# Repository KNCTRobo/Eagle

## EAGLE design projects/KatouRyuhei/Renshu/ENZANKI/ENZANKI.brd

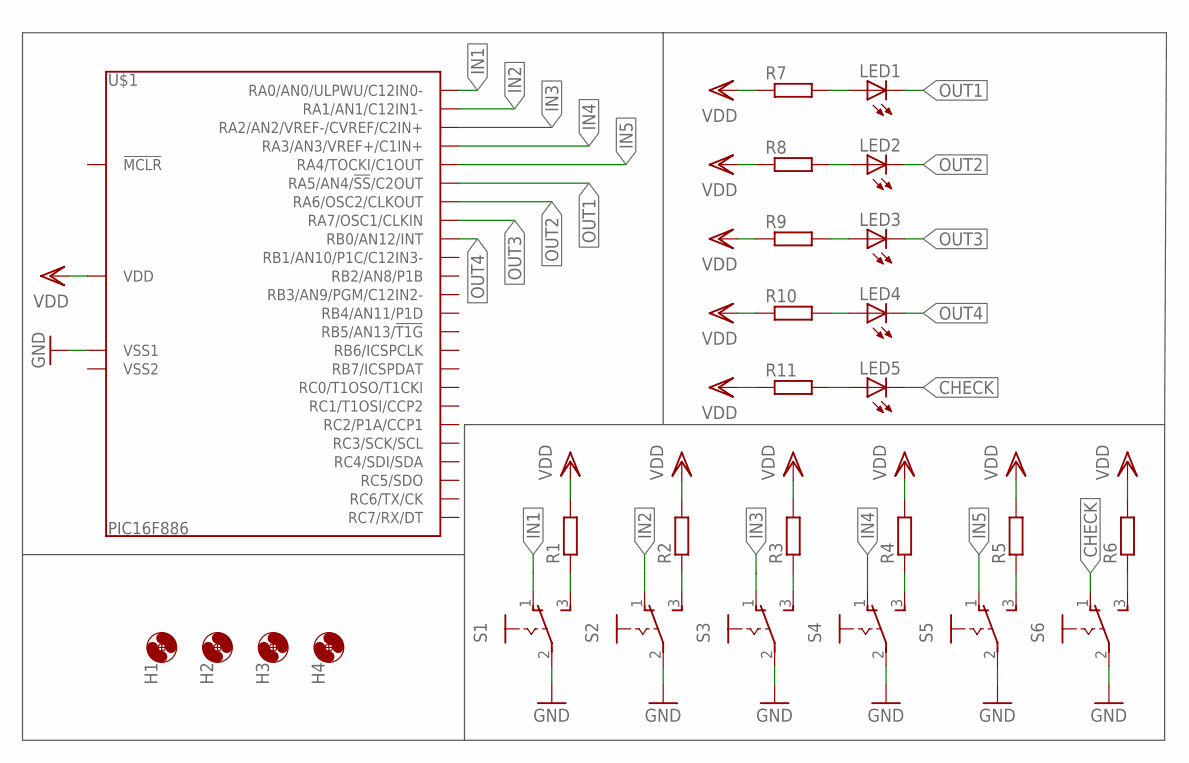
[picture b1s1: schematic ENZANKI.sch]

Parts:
H1, H2, H3, H4: HOLE3.3M3BOLT; HOLE3.3
LED1, LED2, LED3, LED4, LED5: LED5MM
R1, R2, R3, R4, R5, R6, R7, R8, R9, R10, R11: R-EU_R3216W; R3216W
S1, S2, S3, S4, S5, S6: SLIDESW
U$1: PIC16F886; DIL28

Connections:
CHECK: LED5.K (C), S6.1
GND: S1.2, S2.2, S3.2, S4.2, S5.2, S6.2, U$1.8 (VSS1)
IN1: S1.1, U$1.2 (RA0/AN0/ULPWU/C12IN0-)
IN2: S2.1, U$1.3 (RA1/AN1/C12IN1-)
IN3: S3.1, U$1.4 (RA2/AN2/VREF-/CVREF/C2IN+)
IN4: S4.1, U$1.5 (RA3/AN3/VREF+/C1IN+)
IN5: S5.1, U$1.6 (RA4/TOCKI/C1OUT)
unnamed: LED1.A, R7.2
unnamed: LED2.A, R8.2
unnamed: LED3.A, R9.2
unnamed: LED4.A, R10.2
unnamed: R6.1, S6.3
unnamed: R2.1, S2.3
unnamed: R3.1, S3.3
unnamed: R4.1, S4.3
unnamed: LED5.A, R11.2
unnamed: R5.1, S5.3
OUT1: LED1.K (C), U$1.7 (RA5/AN4/!SS!/C2OUT)
OUT2: LED2.K (C), U$1.10 (RA6/OSC2/CLKOUT)
OUT3: LED3.K (C), U$1.9 (RA7/OSC1/CLKIN)
OUT4: LED4.K (C), U$1.21 (RB0/AN12/INT)
R1: R1.1, S1.3
VDD: R1.2, R2.2, R3.2, R4.2, R5.2, R6.2, R7.1, R8.1, R9.1, R10.1, R11.1, U$1.20 (VDD)

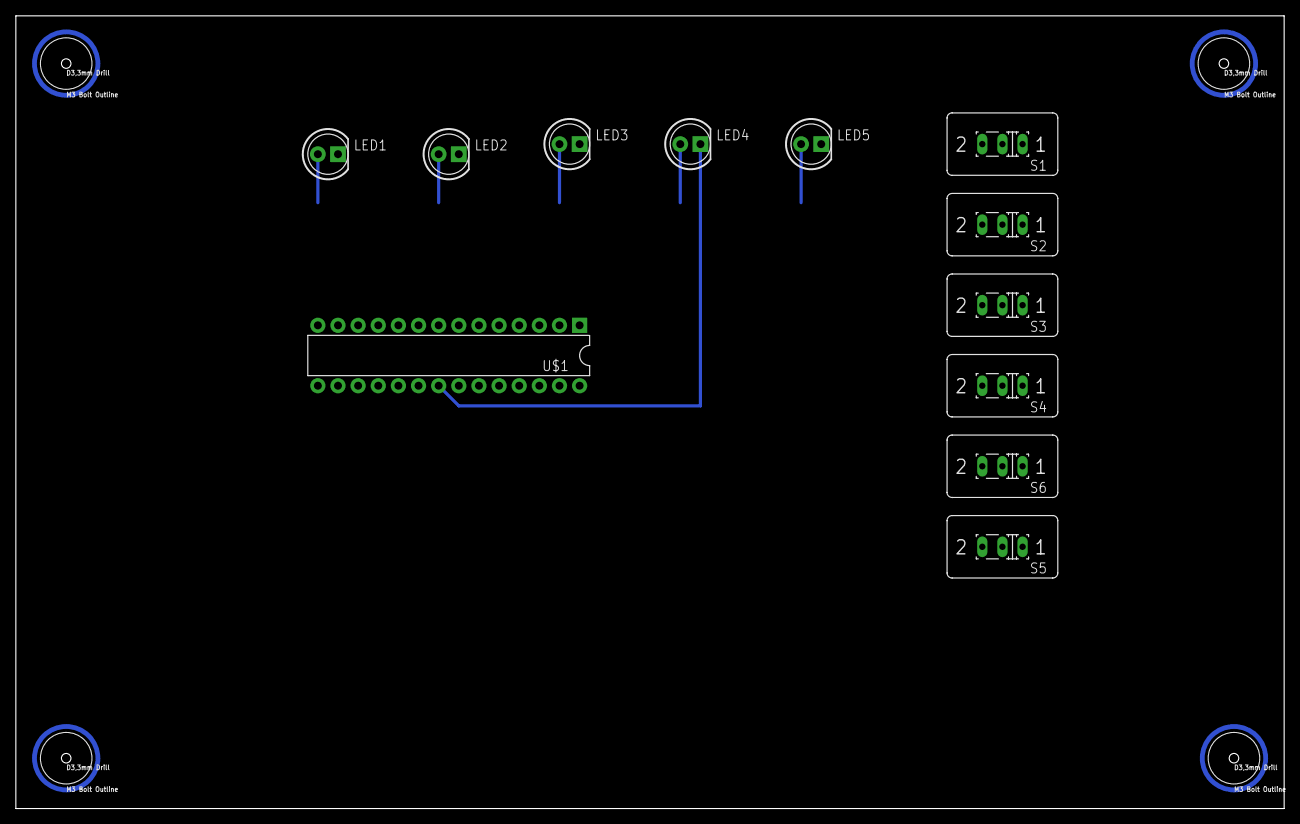
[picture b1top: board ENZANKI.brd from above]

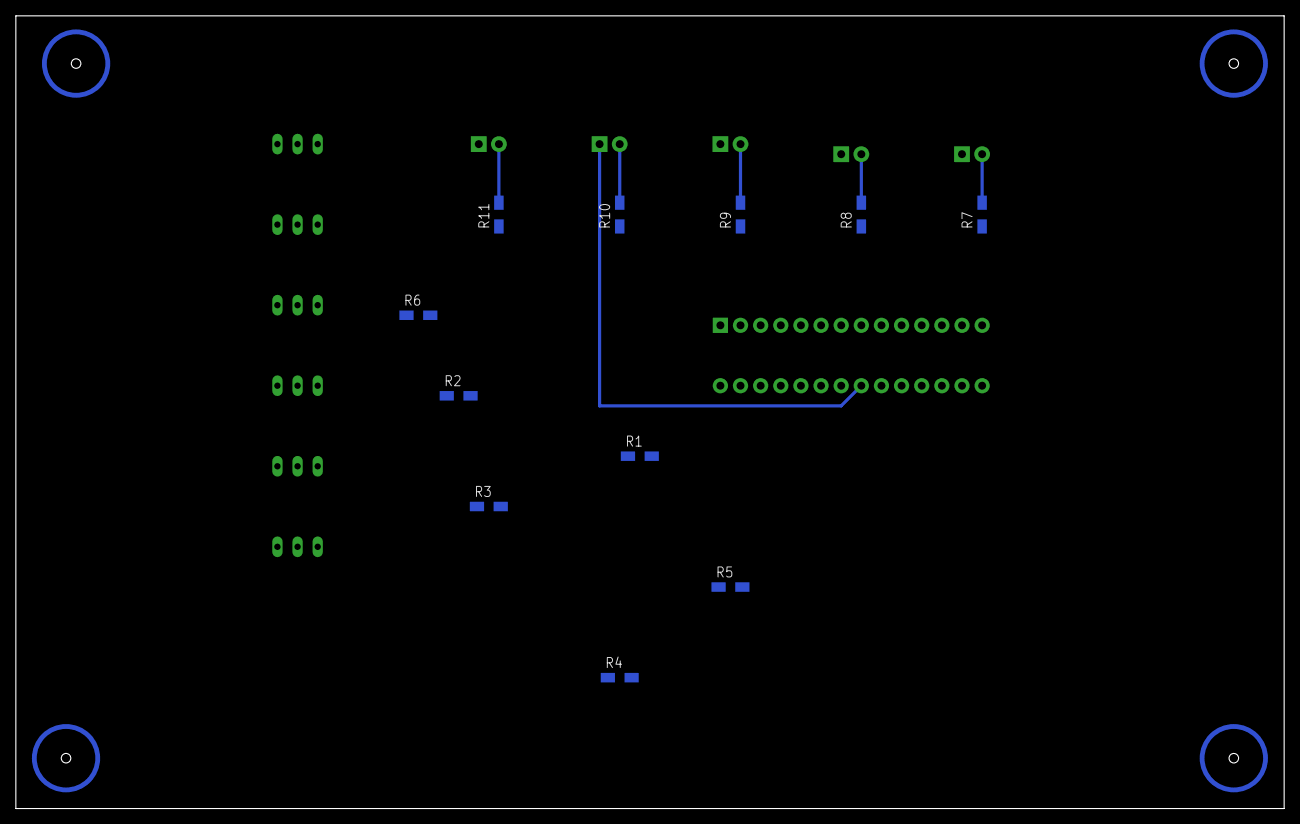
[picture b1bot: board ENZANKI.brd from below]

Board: 2 copper layers, 160.0 x 100.0 mm, 27 parts (11 on the bottom side), 23 nets.

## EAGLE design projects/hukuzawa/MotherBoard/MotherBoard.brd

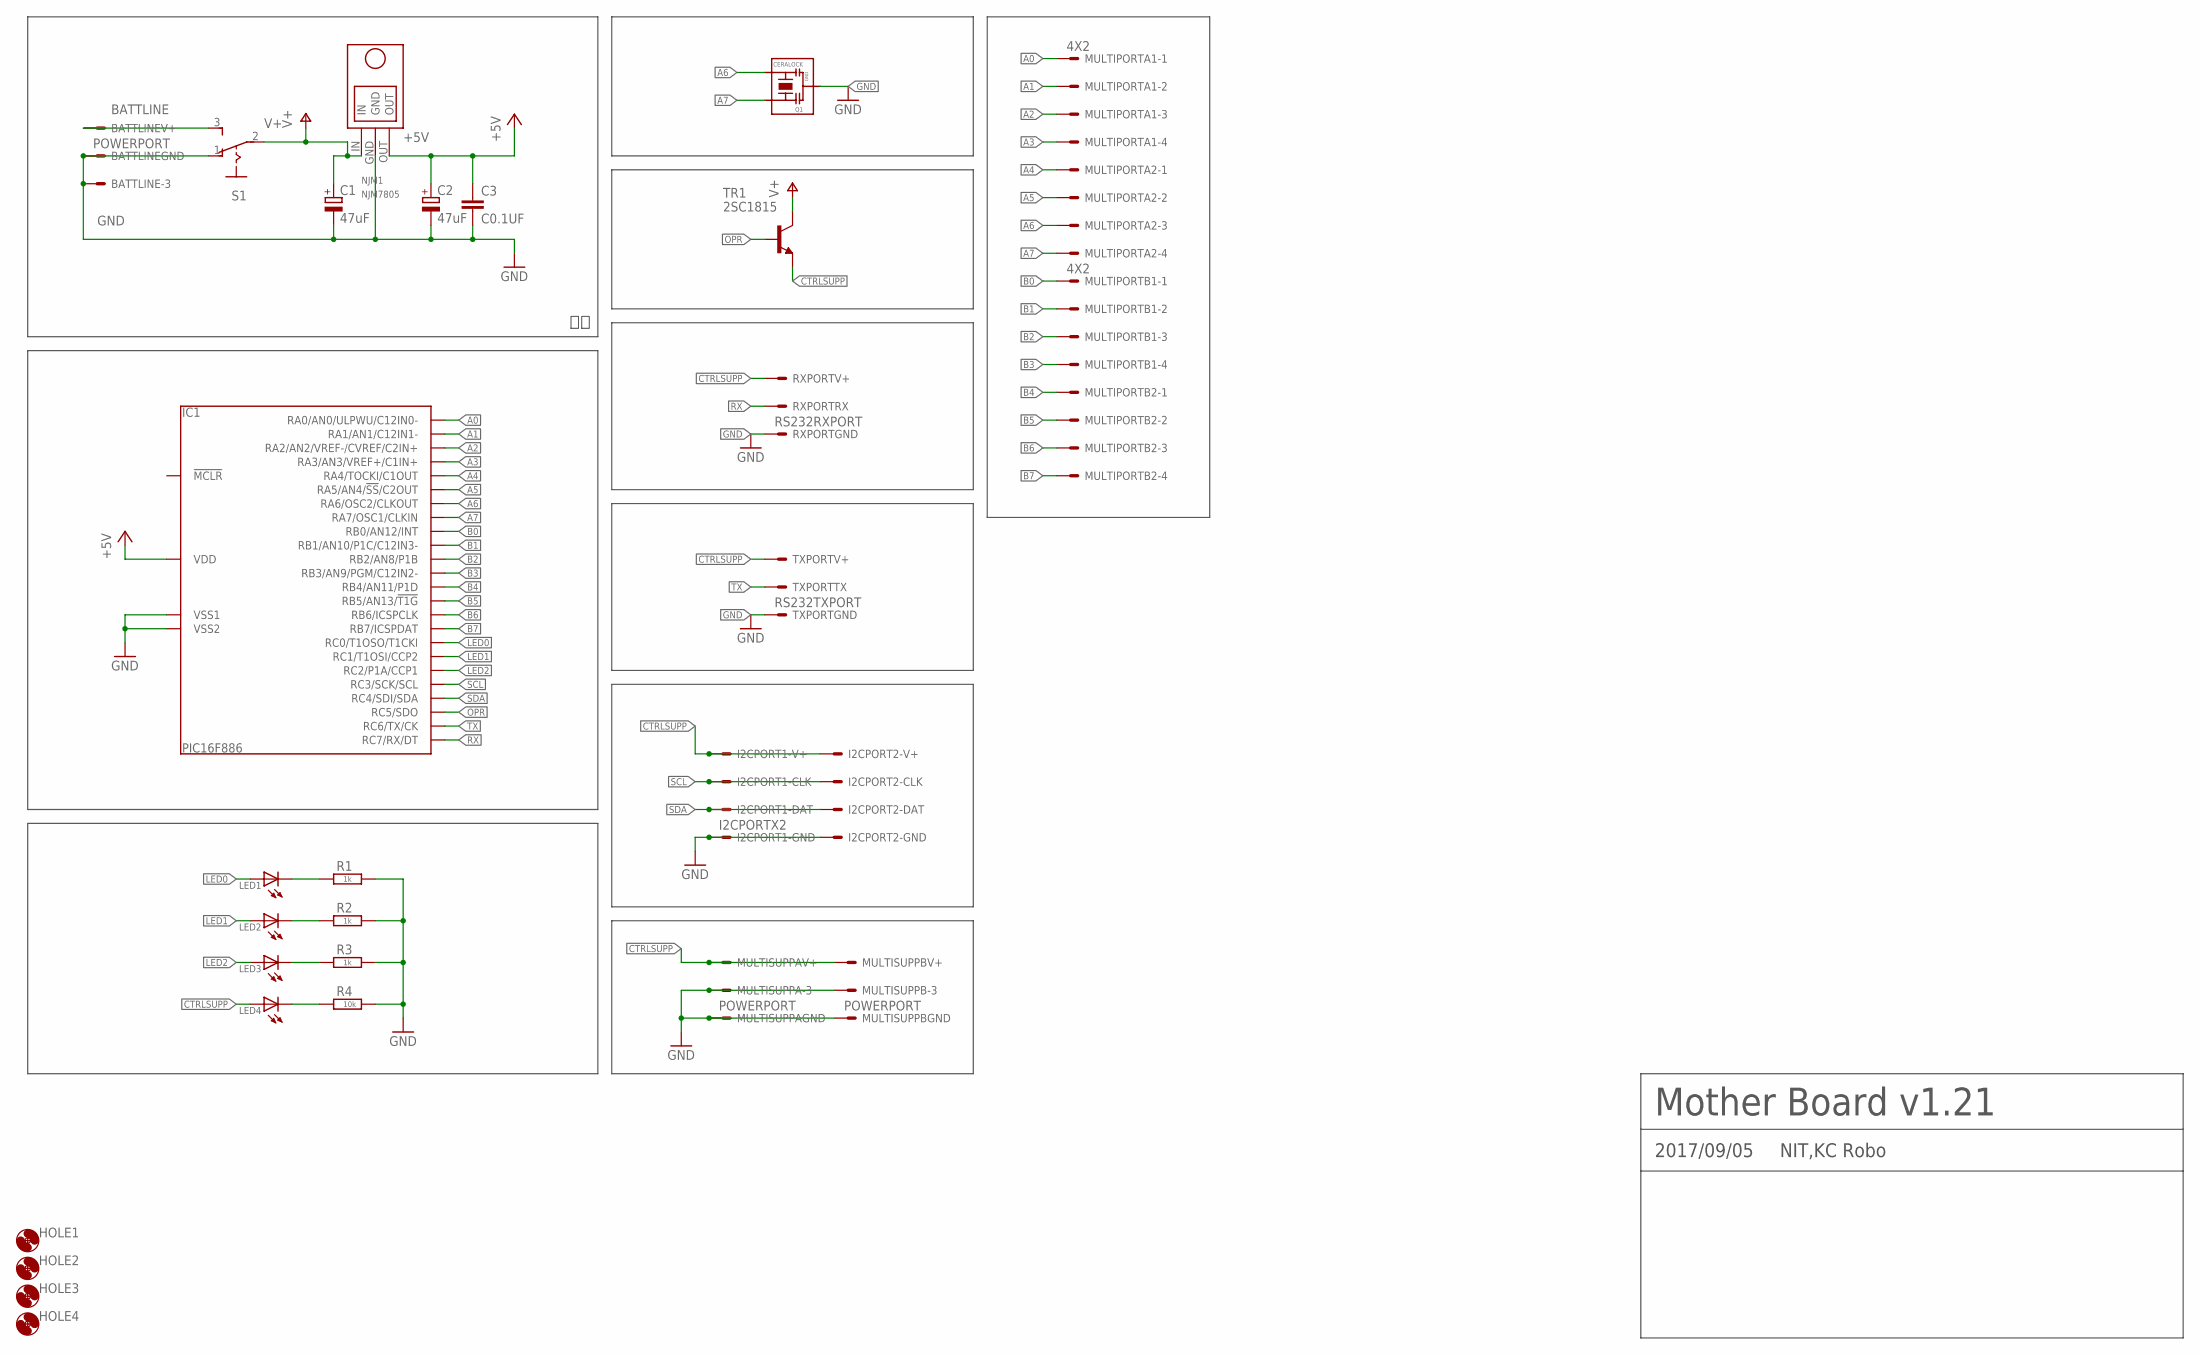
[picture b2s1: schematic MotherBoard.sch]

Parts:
BATTLINE: POWERPORT; 37203-62A3-003
C1, C2: 47uF; E2-5
C3: C0.1UF
HOLE1, HOLE2, HOLE3, HOLE4: HOLE3.3M3BOLT; HOLE3.3
I2CPORT: I2CPORTX2; 37208-62A3-004
IC1: PIC16F886; DIL28
LED1, LED2, LED3, LED4: LED5MM
MULTIPORTA: 4X2; 37208-62A3-004
MULTIPORTB: 4X2; 37208-62A3-004
MULTISUPPA: POWERPORT; 37203-62A3-003
MULTISUPPB: POWERPORT; 37203-62A3-003
NJM1: NJM7805
Q1: CERALOCK
R1, R2, R3: 1k; R3216W
R4: 10k; R3216W
RXPORT: RS232RXPORT; 37203-62A3-003
S1: SLIDESW
TR1: 2SC1815; TO92-
TXPORT: RS232TXPORT; 37203-62A3-003

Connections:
+5V: C2.+, C3.1, IC1.20 (VDD), NJM1.OUT
A0: IC1.2 (RA0/AN0/ULPWU/C12IN0-), MULTIPORTA.1-1
A1: IC1.3 (RA1/AN1/C12IN1-), MULTIPORTA.1-2
A2: IC1.4 (RA2/AN2/VREF-/CVREF/C2IN+), MULTIPORTA.1-3
A3: IC1.5 (RA3/AN3/VREF+/C1IN+), MULTIPORTA.1-4
A4: IC1.6 (RA4/TOCKI/C1OUT), MULTIPORTA.2-1
A5: IC1.7 (RA5/AN4/!SS!/C2OUT), MULTIPORTA.2-2
A6: IC1.10 (RA6/OSC2/CLKOUT), MULTIPORTA.2-3, Q1.P$3
A7: IC1.9 (RA7/OSC1/CLKIN), MULTIPORTA.2-4, Q1.P$1
B0: IC1.21 (RB0/AN12/INT), MULTIPORTB.1-1
B1: IC1.22 (RB1/AN10/P1C/C12IN3-), MULTIPORTB.1-2
B2: IC1.23 (RB2/AN8/P1B), MULTIPORTB.1-3
B3: IC1.24 (RB3/AN9/PGM/C12IN2-), MULTIPORTB.1-4
B4: IC1.25 (RB4/AN11/P1D), MULTIPORTB.2-1
B5: IC1.26 (RB5/AN13/!T1G), MULTIPORTB.2-2
B6: IC1.27 (RB6/ICSPCLK), MULTIPORTB.2-3
B7: IC1.28 (RB7/ICSPDAT), MULTIPORTB.2-4
BATTLINE: BATTLINE.1-2, S1.3
CTRLSUPP: I2CPORT.1-2, I2CPORT.2-2, LED4.A, MULTISUPPA.1-2, MULTISUPPB.1-2, RXPORT.1-2, TR1.E, TXPORT.1-2
GND: BATTLINE.1-1, BATTLINE.1-3, C1.-, C2.-, C3.2, I2CPORT.1-1, I2CPORT.2-1, IC1.8 (VSS1), IC1.19 (VSS2), MULTISUPPA.1-1, MULTISUPPA.1-3, MULTISUPPB.1-1, MULTISUPPB.1-3, NJM1.GND, Q1.P$2, R1.2, R2.2, R3.2, R4.2, RXPORT.1-1, S1.1, TXPORT.1-1
LED0: IC1.11 (RC0/T1OSO/T1CKI), LED1.A
LED1: IC1.12 (RC1/T1OSI/CCP2), LED2.A
LED2: IC1.13 (RC2/P1A/CCP1), LED3.A
unnamed: LED1.K (C), R1.1
unnamed: LED2.K (C), R2.1
unnamed: LED3.K (C), R3.1
unnamed: LED4.K (C), R4.1
OPR: IC1.16 (RC5/SDO), TR1.B
RX: IC1.18 (RC7/RX/DT), RXPORT.1-3
SCL: I2CPORT.1-3, I2CPORT.2-3, IC1.14 (RC3/SCK/SCL)
SDA: I2CPORT.1-4, I2CPORT.2-4, IC1.15 (RC4/SDI/SDA)
TX: IC1.17 (RC6/TX/CK), TXPORT.1-3
V+: C1.+, NJM1.IN, S1.2, TR1.C

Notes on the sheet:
Mother Board v1.21
NIT,KC Robo
2017/09/05

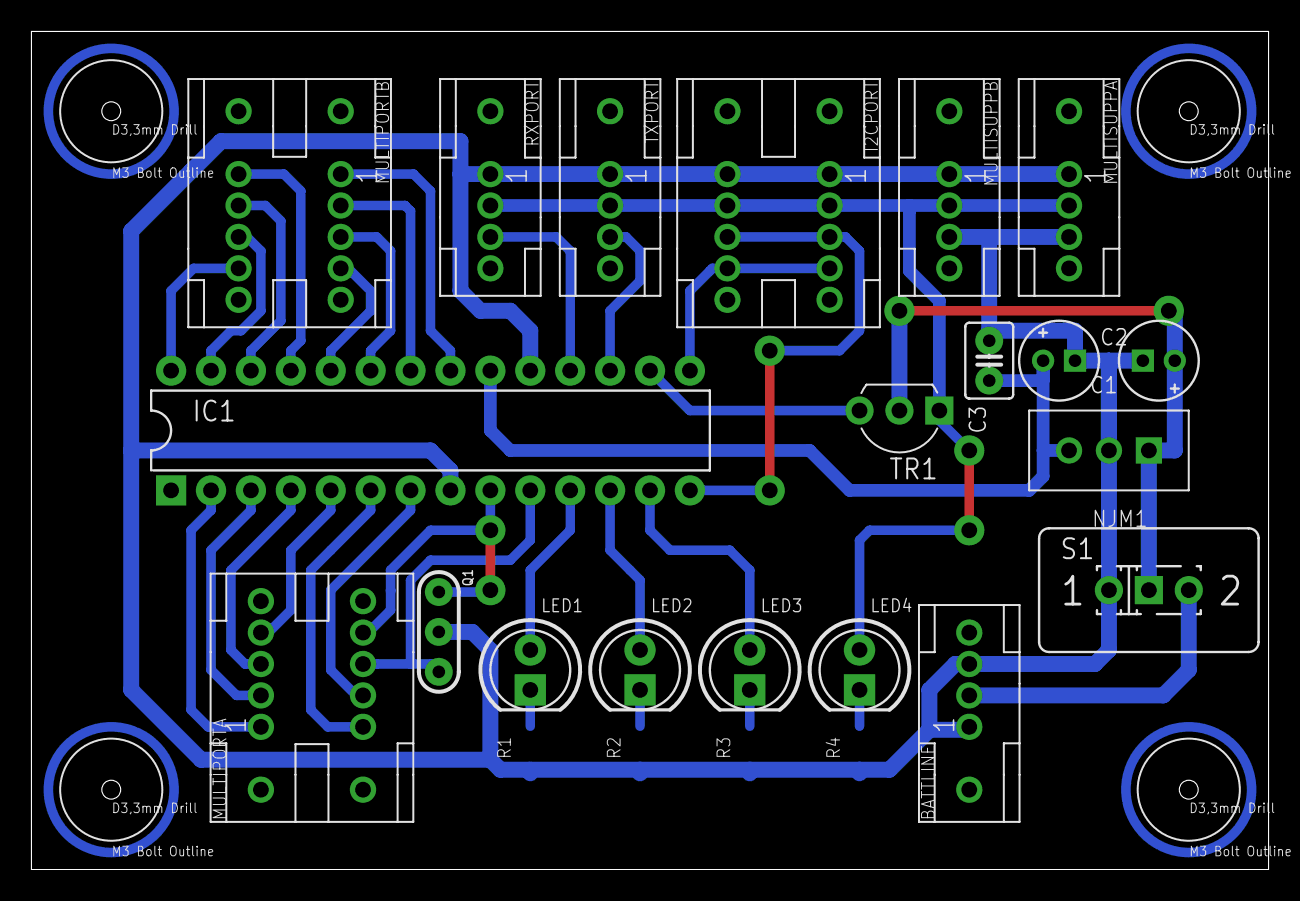
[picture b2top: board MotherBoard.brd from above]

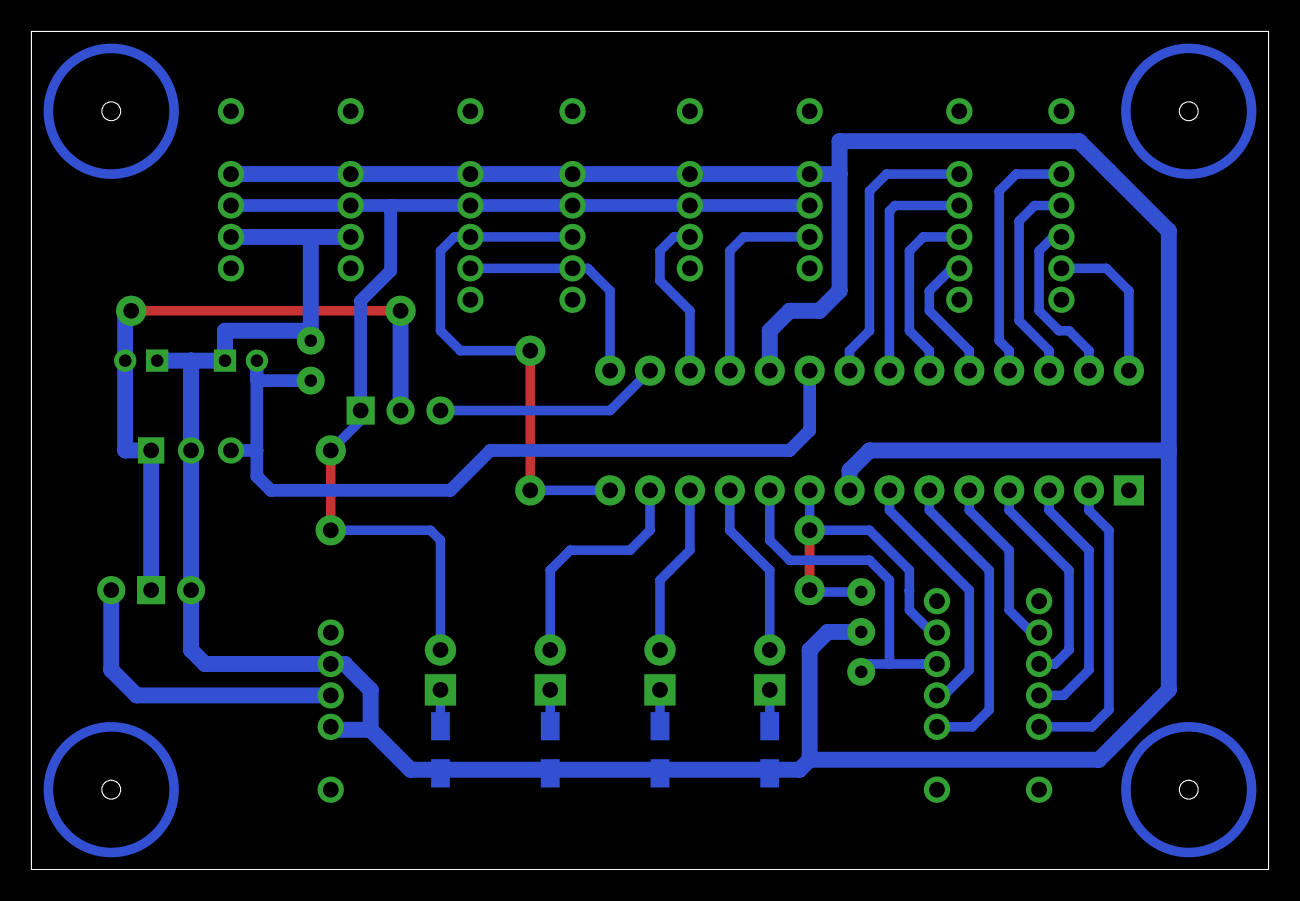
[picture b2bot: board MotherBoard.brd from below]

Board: 2 copper layers, 78.7 x 53.3 mm, 28 parts (4 on the bottom side), 33 nets.

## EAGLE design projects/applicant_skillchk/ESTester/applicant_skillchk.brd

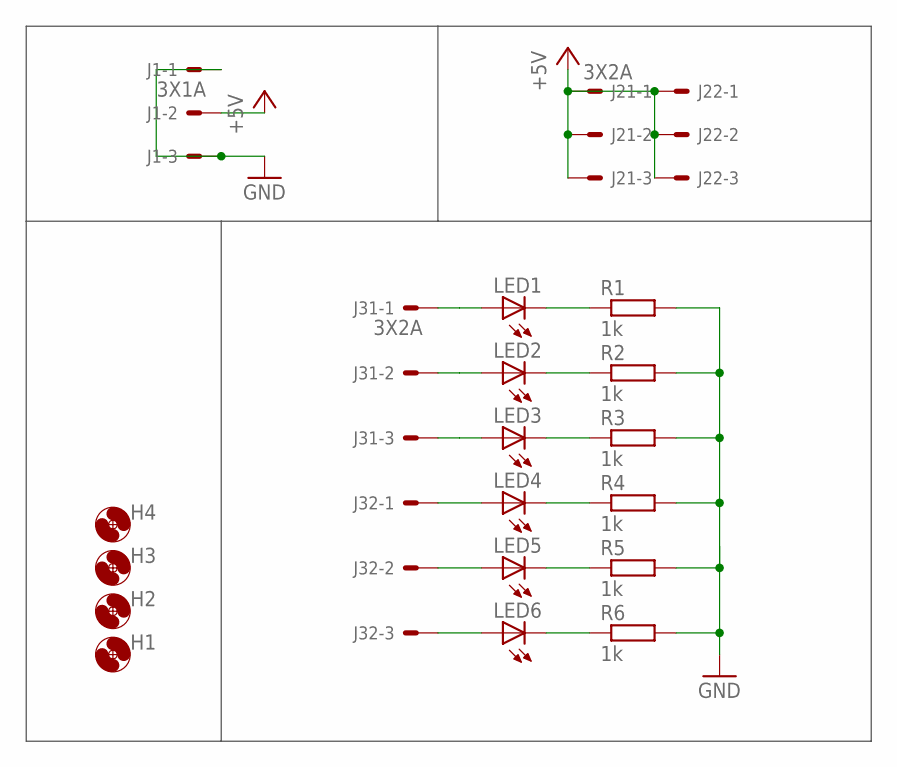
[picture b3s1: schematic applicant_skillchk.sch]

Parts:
H1, H2, H3, H4: HOLE3.3M3BOLT; HOLE3.3
J1: 3X1A; 37203-62A3-003
J2, J3: 3X2A; 37206-62A3-003
LED1, LED2, LED3, LED4, LED5, LED6: LED5MM
R1, R2, R3, R4, R5, R6: 1k; R3216W

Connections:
+5V: J1.1-2, J2.1-1, J2.1-2, J2.1-3, J2.2-1, J2.2-2, J2.2-3
GND: J1.1-1, J1.1-3, R1.2, R2.2, R3.2, R4.2, R5.2, R6.2
unnamed: LED1.K (C), R1.1
unnamed: LED2.K (C), R2.1
unnamed: LED3.K (C), R3.1
unnamed: LED4.K (C), R4.1
unnamed: LED5.K (C), R5.1
unnamed: LED6.K (C), R6.1
unnamed: J3.1-1, LED1.A
unnamed: J3.1-2, LED2.A
unnamed: J3.1-3, LED3.A
unnamed: J3.2-1, LED4.A
unnamed: J3.2-2, LED5.A
unnamed: J3.2-3, LED6.A

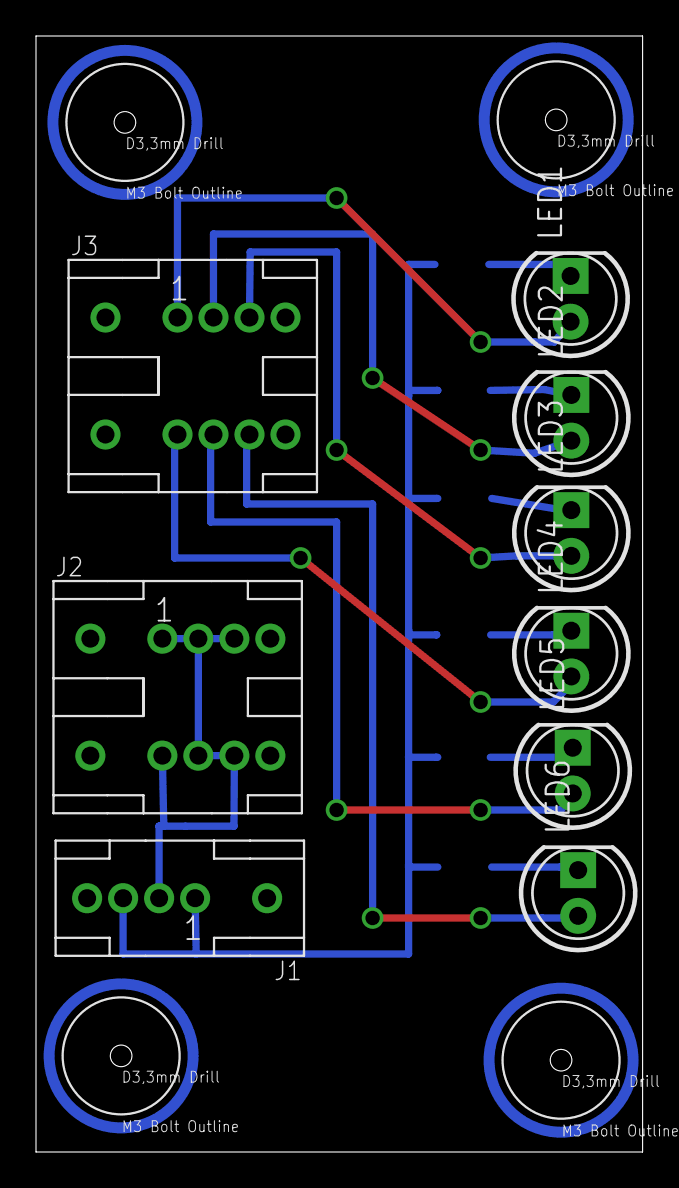
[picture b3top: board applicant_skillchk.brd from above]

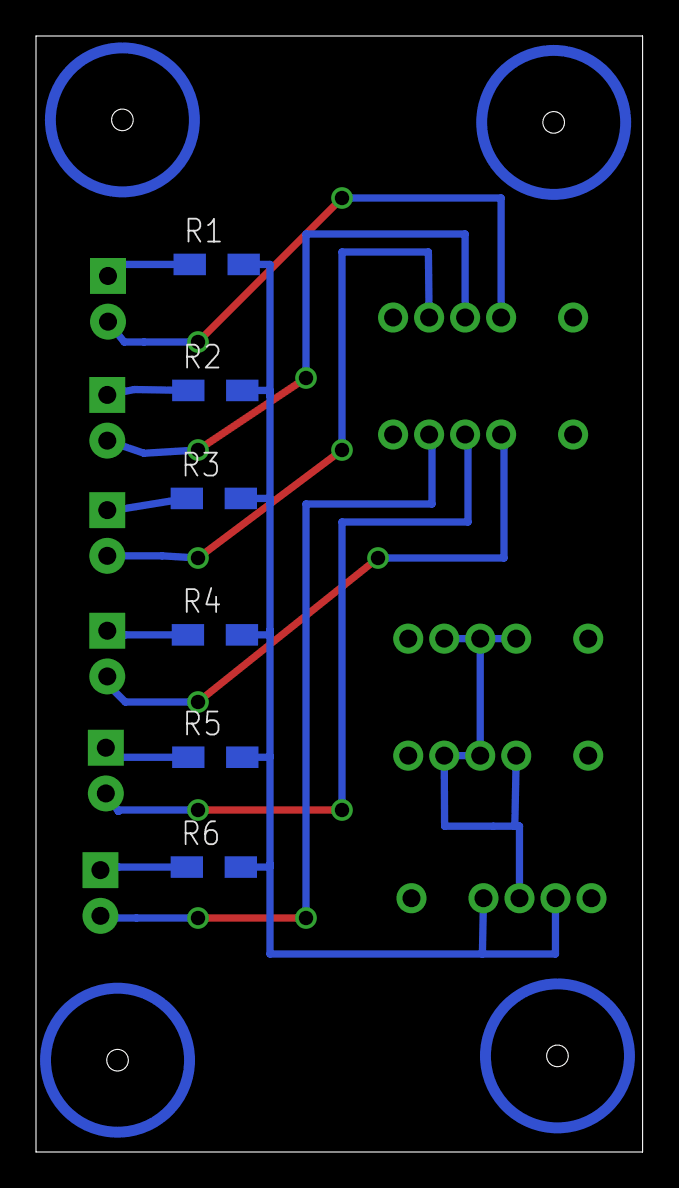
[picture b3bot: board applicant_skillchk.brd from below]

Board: 2 copper layers, 33.7 x 62.0 mm, 19 parts (6 on the bottom side), 14 nets.

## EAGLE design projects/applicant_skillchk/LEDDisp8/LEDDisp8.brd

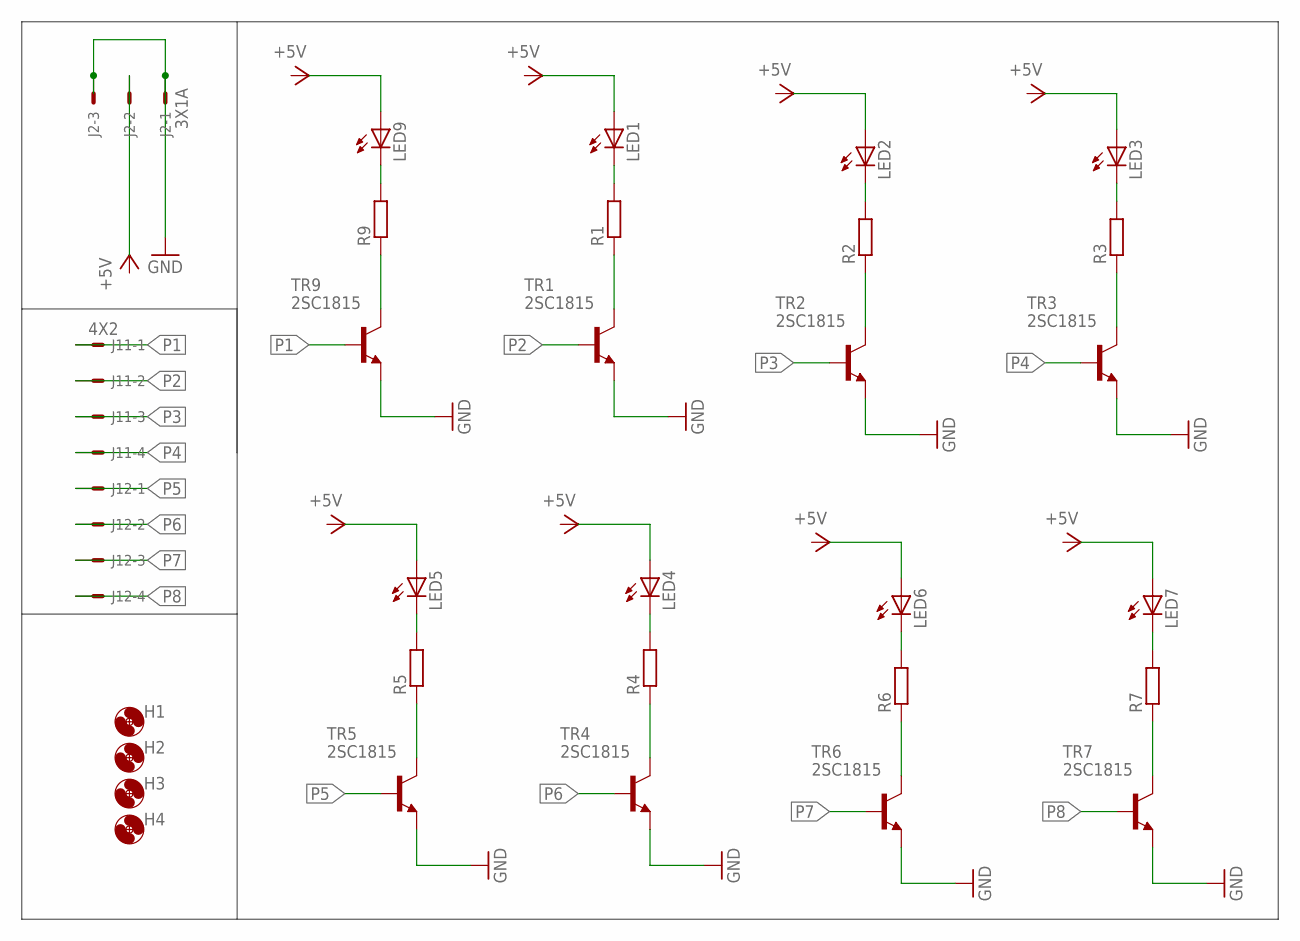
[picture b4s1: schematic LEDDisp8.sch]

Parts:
H1, H2, H3, H4: HOLE3.3M3BOLT; HOLE3.3
J1: 4X2; 37208-62A3-004
J2: 3X1A; 37203-62A3-003
LED1, LED2, LED3, LED4, LED5, LED6, LED7, LED9: LED3MM
R1, R2, R3, R4, R5, R6, R7, R9: R-EU_R3216W; R3216W
TR1, TR2, TR3, TR4, TR5, TR6, TR7, TR9: 2SC1815; TO92-

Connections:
GND: J2.1-1, J2.1-3, TR1.E, TR2.E, TR3.E, TR4.E, TR5.E, TR6.E, TR7.E, TR9.E
unnamed: R1.1, TR1.C
unnamed: R9.1, TR9.C
unnamed: LED9.K (C), R9.2
unnamed: R2.1, TR2.C
unnamed: R3.1, TR3.C
unnamed: R4.1, TR4.C
unnamed: R5.1, TR5.C
unnamed: R6.1, TR6.C
unnamed: R7.1, TR7.C
unnamed: LED1.K (C), R1.2
unnamed: LED2.K (C), R2.2
unnamed: LED6.K (C), R6.2
unnamed: LED3.K (C), R3.2
unnamed: LED4.K (C), R4.2
unnamed: LED7.K (C), R7.2
unnamed: LED5.K (C), R5.2
P1: J1.1-1, TR9.B
P2: J1.1-2, TR1.B
P3: J1.1-3, TR2.B
P4: J1.1-4, TR3.B
P5: J1.2-1, TR5.B
P6: J1.2-2, TR4.B
P7: J1.2-3, TR6.B
P8: J1.2-4, TR7.B

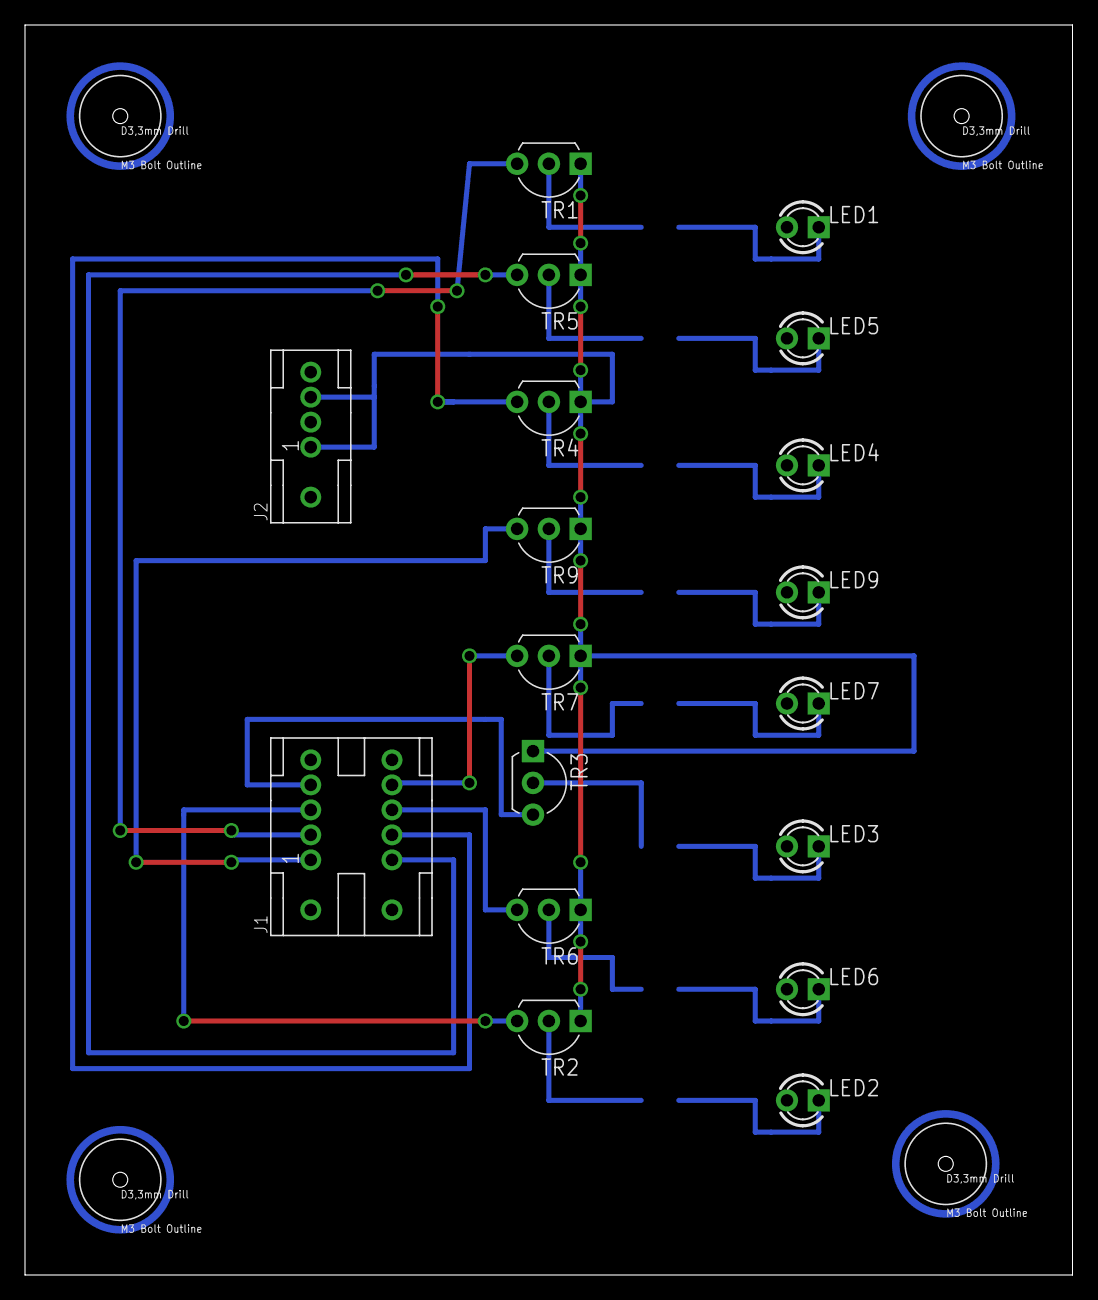
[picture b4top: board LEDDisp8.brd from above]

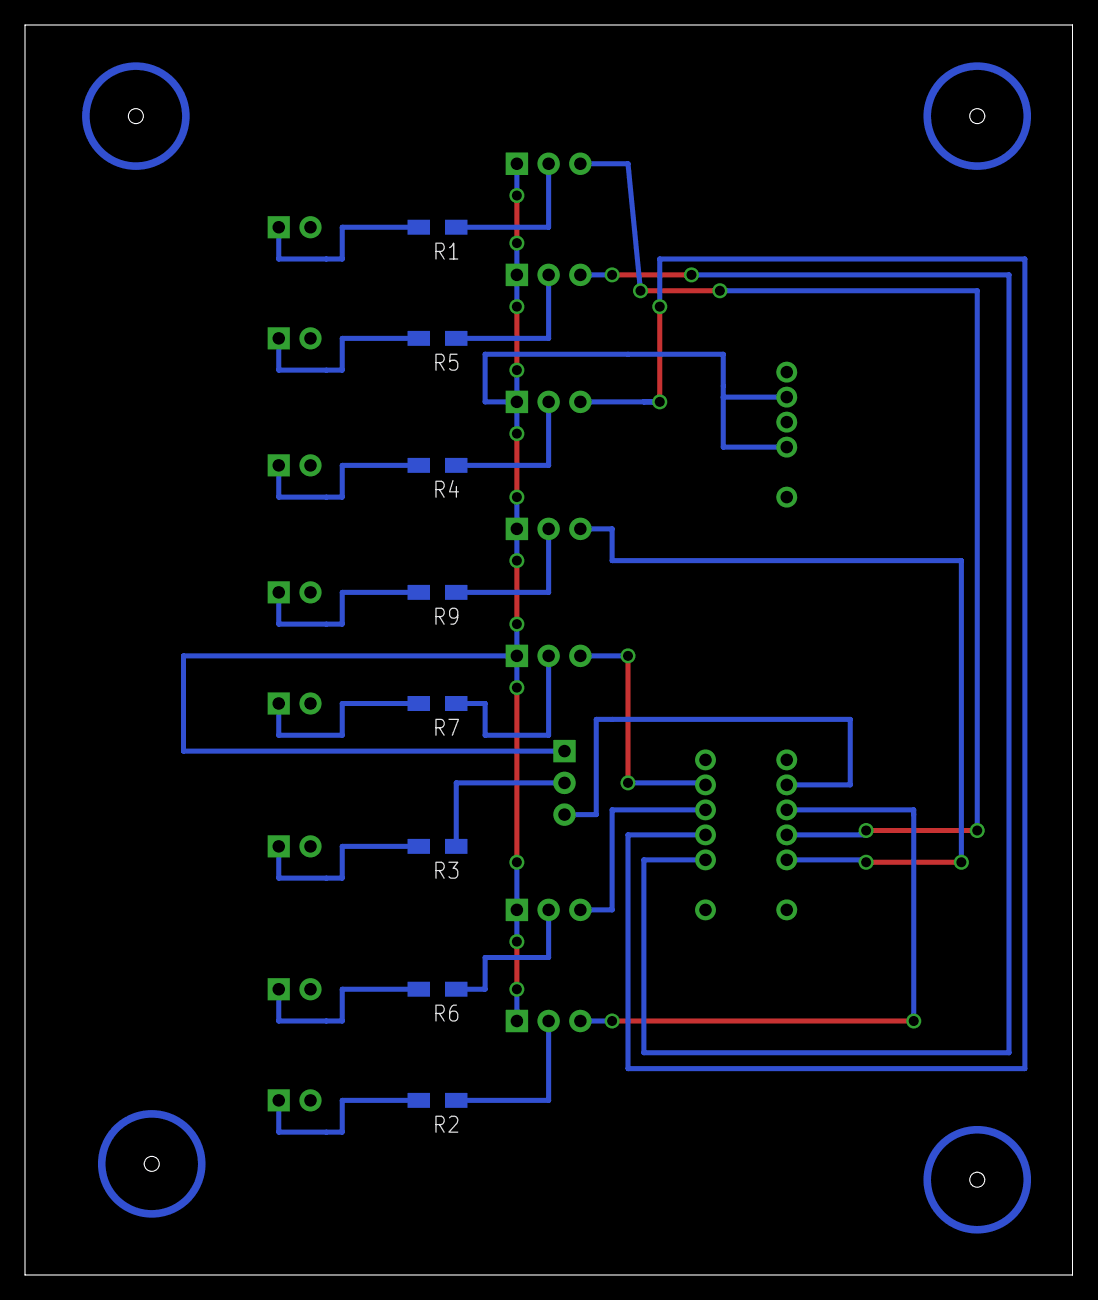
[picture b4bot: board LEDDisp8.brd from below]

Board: 2 copper layers, 83.8 x 100.0 mm, 30 parts (8 on the bottom side), 25 nets.

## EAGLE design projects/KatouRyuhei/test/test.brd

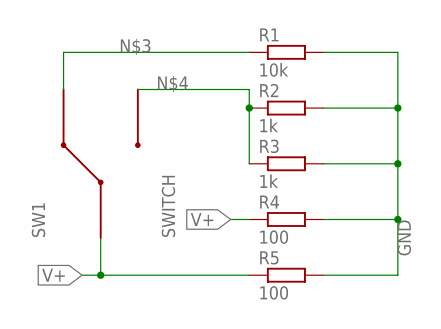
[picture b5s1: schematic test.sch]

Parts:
R1: 10k; R3216W
R2, R3: 1k; R3216W
R4, R5: 100; R3216W
SW1: SWITCH; SW3

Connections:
GND: R1.2, R2.2, R3.2, R4.2, R5.2
unnamed: R1.1, SW1.P1
unnamed: R2.1, R3.1, SW1.P3
V+: R4.1, R5.1, SW1.P2

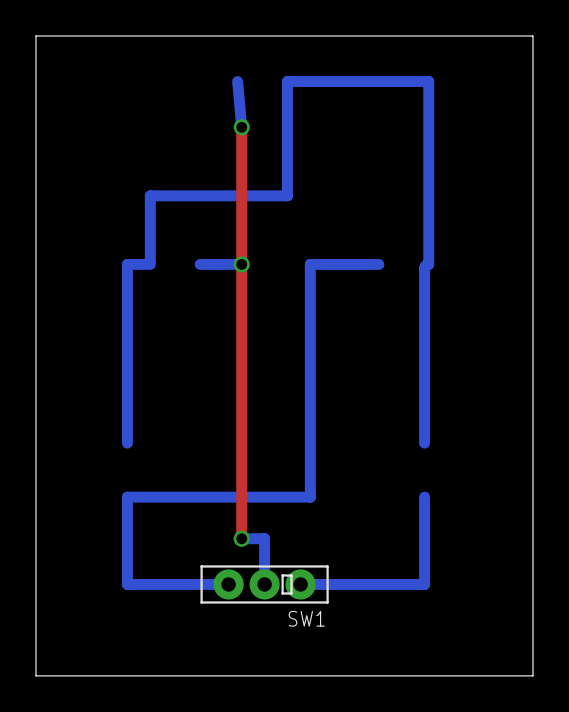
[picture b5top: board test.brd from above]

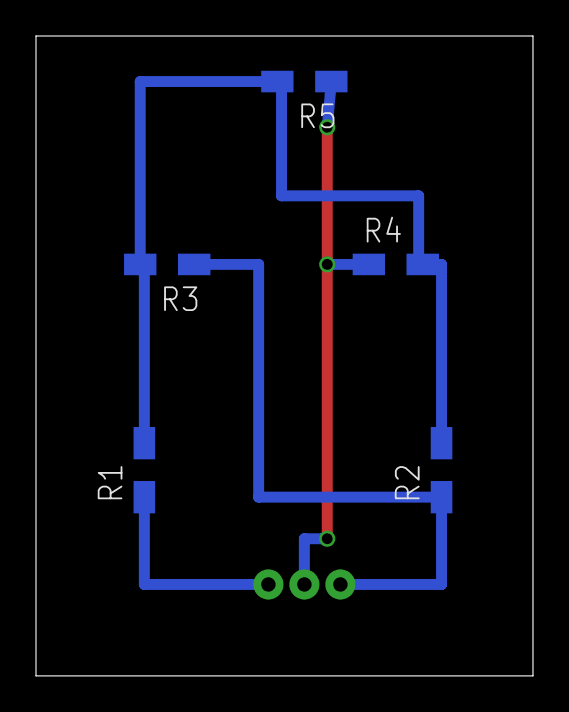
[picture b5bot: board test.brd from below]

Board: 2 copper layers, 27.6 x 35.5 mm, 6 parts (5 on the bottom side), 4 nets.

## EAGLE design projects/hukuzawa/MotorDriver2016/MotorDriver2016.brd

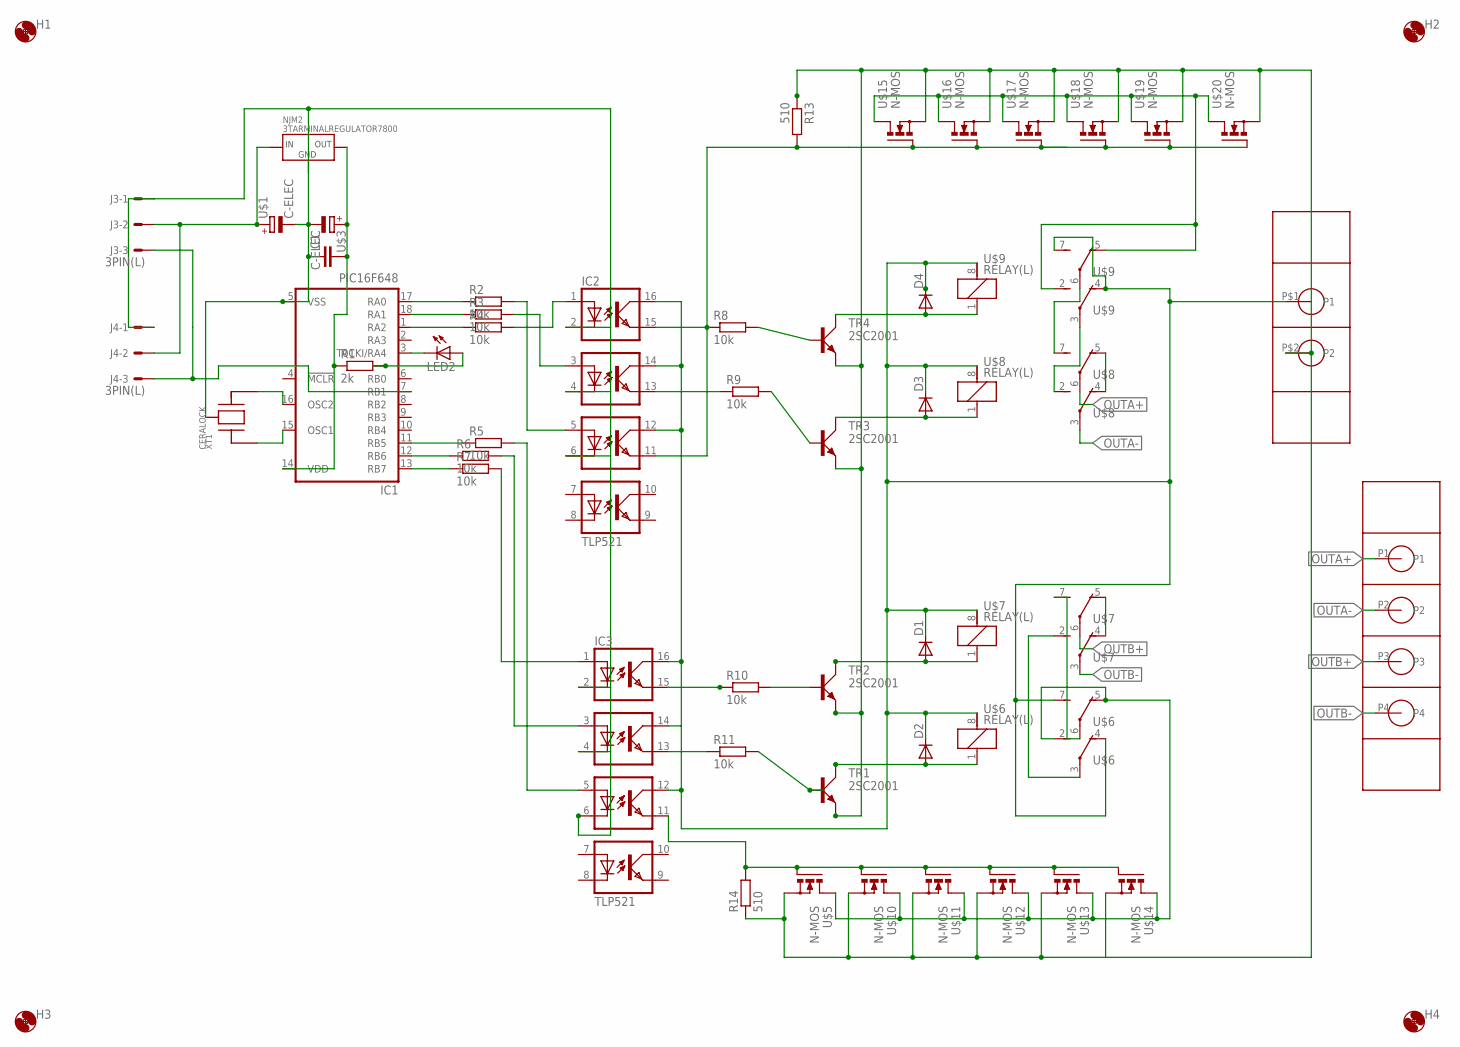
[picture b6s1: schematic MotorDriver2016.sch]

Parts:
C1: C-; C-2.54
D1, D2, D3, D4: DIODE7.5
H1, H2, H3, H4: HOLE3.3M3BOLT; HOLE3.3
IC1: PIC16F648; DIL18
IC2, IC3: TLP521; DIL16
J3, J4: 3PIN(L); 3PL
LED2: LED5MM
NJM2: 3TARMINALREGULATOR7800; TO-220
R1: 2k; R3216W
R2, R3, R4, R5, R6, R7, R8, R9, R10, R11: 10k; R3216W
R13, R14: 510; R3216W
TR1, TR2, TR3, TR4: 2SC2001; TO92BCE
U$1, U$3: C-ELEC; C-6MM
U$2: BP341L
U$4: BP341L_1; BP341L
U$5, U$10, U$11, U$12, U$13, U$14, U$15, U$16, U$17, U$18, U$19, U$20: N-MOS; TO220BV
U$6, U$7, U$8, U$9: RELAY(L); G2R2
XT1: CERALOCK

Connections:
5V: C1.P$2 (2), IC1.14 (VDD), NJM2.OUT, R1.1, U$3.+
9V: J3.2, J4.2, NJM2.IN, U$1.+
12V: D1.PK (C), D2.PK (C), D3.PK (C), D4.PK (C), IC2.12 (COL2), IC2.14 (COL1), IC2.16 (COL0), IC3.12 (COL2), IC3.14 (COL1), IC3.16 (COL0), U$4.P$1 (P1), U$6.4 (O), U$6.7 (S), U$6.8 (2), U$7.8 (2), U$8.8 (2), U$9.4 (O), U$9.7 (S), U$9.8 (2)
FET_D1: U$9.2 (S), U$9.5 (O), U$15.D, U$16.D, U$17.D, U$18.D, U$19.D, U$20.D
FET_G1: IC2.11 (EMIT2), R13.2, U$15.G, U$16.G, U$17.G, U$18.G, U$19.G, U$20.G
FET_G2: IC3.11 (EMIT2), R14.2, U$5.G, U$10.G, U$11.G, U$12.G, U$13.G, U$14.G
GND1: C1.P$1 (1), IC1.5 (VSS), IC2.2 (C0), IC2.4 (C1), IC2.6 (C2), IC3.2 (C0), IC3.4 (C1), IC3.6 (C2), J3.1, J4.1, NJM2.GND, U$1.-, U$3.-, XT1.P2 (2)
GND2: R13.1, R14.1, TR1.E, TR2.E, TR3.E, TR4.E, U$4.P$2 (P2), U$5.S, U$10.S, U$11.S, U$12.S, U$13.S, U$14.S, U$15.S, U$16.S, U$17.S, U$18.S, U$19.S, U$20.S
LED_A: LED2.A, R1.2
LED_C: IC1.3 (T0CKI/RA4), LED2.K (C)
unnamed: IC1.16 (OSC2), XT1.P3 (3)
unnamed: IC1.15 (OSC1), XT1.P1 (1)
unnamed: IC1.17 (RA0), R2.1
unnamed: IC1.18 (RA1), R3.1
unnamed: IC1.1 (RA2), R4.1
unnamed: IC1.13 (RB7), R7.1
unnamed: IC1.12 (RB6), R6.1
unnamed: IC1.11 (RB5), R5.1
unnamed: IC2.5 (A2), R2.2
unnamed: IC2.3 (A1), R3.2
unnamed: IC2.1 (A0), R4.2
unnamed: IC3.1 (A0), R7.2
unnamed: IC3.3 (A1), R6.2
unnamed: IC3.5 (A2), R5.2
unnamed: IC2.15 (EMIT0), R8.1
unnamed: IC2.13 (EMIT1), R9.1
unnamed: IC3.15 (EMIT0), R10.1
unnamed: IC3.13 (EMIT1), R11.1
unnamed: R11.2, TR1.B
unnamed: D4.PA (A), TR4.C, U$9.1
unnamed: D3.PA (A), TR3.C, U$8.1
unnamed: D1.PA (A), TR2.C, U$7.1
unnamed: D2.PA (A), TR1.C, U$6.1
unnamed: U$5.D, U$6.2 (S), U$6.5 (O), U$10.D, U$11.D, U$12.D, U$13.D, U$14.D
unnamed: U$8.7 (S), U$9.6
unnamed: U$8.2 (S), U$9.3
unnamed: U$8.4 (O), U$8.5 (O)
unnamed: R8.2, TR4.B
unnamed: R9.2, TR3.B
unnamed: R10.2, TR2.B
unnamed: U$6.6, U$7.7 (S)
unnamed: U$6.3, U$7.2 (S)
unnamed: U$7.4 (O), U$7.5 (O)
OUTA+: U$2.P1, U$8.6
OUTA-: U$2.P2, U$8.3
OUTB+: U$2.P3, U$7.6
OUTB-: U$2.P4, U$7.3
SIGNAL: IC1.7 (RB1), J3.3, J4.3
